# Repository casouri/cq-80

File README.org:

#+TITLE: CQ-80 Terminal (NAMACO端末) replica

Custom CQ-80 terminal replica! Not only is it 100% accurate, I also added Bluetooth music playback control feature. The shell is 3d printed, and the electronics are made of off-the-shelf parts.

This repository contains all the source files for the 3d model, PCB board design, etc. For a guide on making your own replica, visit: [[https://casouri.github.io/cq-80/guide-en.html][DIY Guide for CQ-80 Replica]].

For more pics, visit [[https://casouri.github.io/cq-80][CQ-80 Replica]].

#+attr_html: :width 100%
[[./docs/img/demo-top.jpeg]]

#+attr_html: :width 100%
[[./docs/img/cq-80 promo.jpg]]

#+attr_html: :width 100%
[[./docs/img/cq-80 screenshot.jpg]]

#+attr_html: :width 100%
[[./docs/img/demo-head-lamp.jpeg]]

#+attr_html: :width 100%
[[./docs/img/demo-side.jpeg]]

#+attr_html: :width 100%
[[./docs/img/demo-top-close-up.jpeg]]

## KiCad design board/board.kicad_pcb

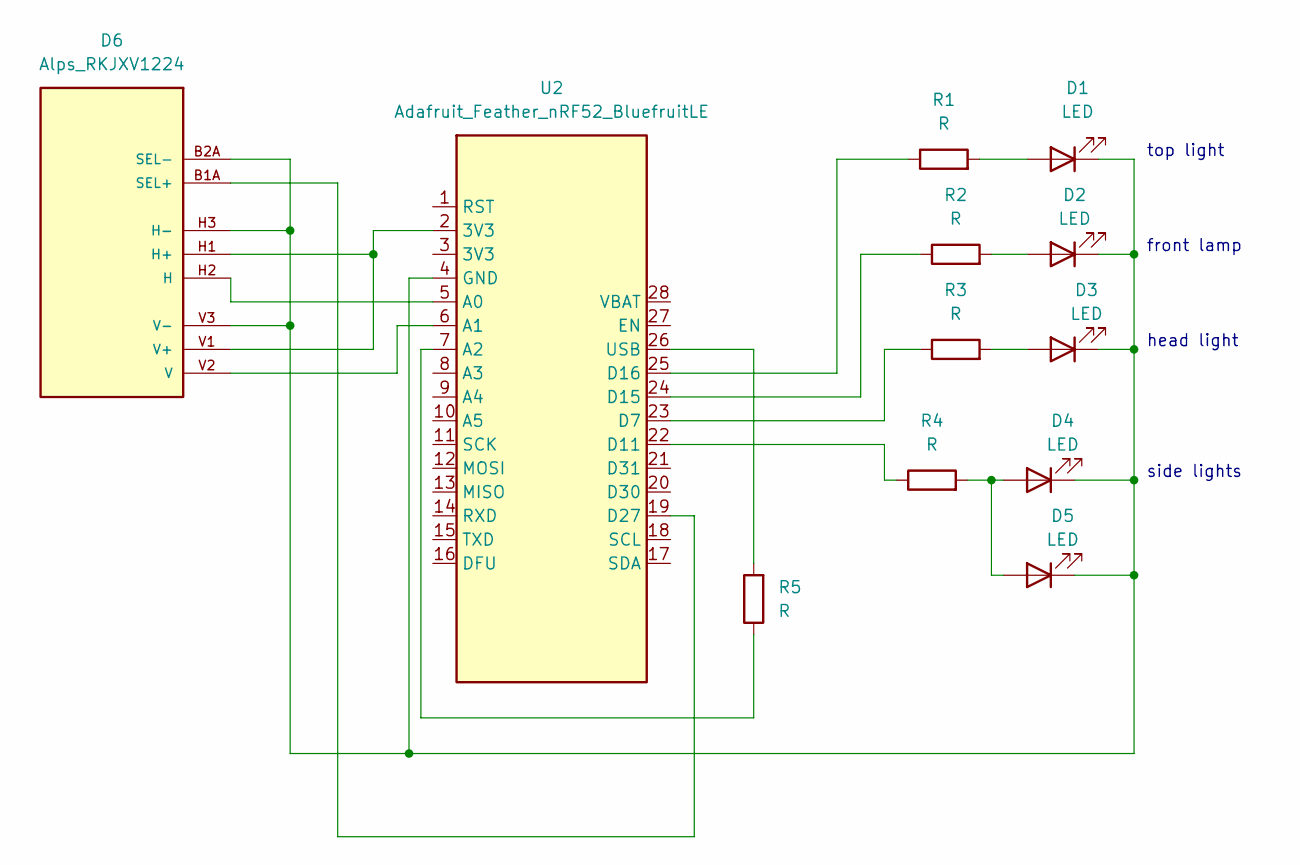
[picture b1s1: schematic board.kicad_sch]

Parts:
D1, D2, D3, D4, D5: LED; LED_D5.0mm_Clear
D6: Alps_RKJXV1224
R1, R2, R3, R4, R5: R; R_Axial_DIN0207_L6.3mm_D2.5mm_P10.16mm_Horizontal
U2: Adafruit_Feather_nRF52_BluefruitLE

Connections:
unnamed: D1.1 (K), D2.1 (K), D3.1 (K), D4.1 (K), D5.1 (K), D6.B2A (SEL-), D6.H3 (H-), D6.V3 (V-), U2.4 (GND)
unnamed: D1.2 (A), R1.2
unnamed: D2.2 (A), R2.2
unnamed: D3.2 (A), R3.2
unnamed: D4.2 (A), D5.2 (A), R4.2
unnamed: D6.B1A (SEL+), U2.19 (D27)
unnamed: D6.H1 (H+), D6.V1 (V+), U2.2 (3V3)
unnamed: D6.H2 (H), U2.5 (A0)
unnamed: D6.V2 (V), U2.6 (A1)
unnamed: R1.1, U2.25 (D16)
unnamed: R2.1, U2.24 (D15)
unnamed: R3.1, U2.23 (D7)
unnamed: R4.1, U2.22 (D11)
unnamed: R5.1, U2.7 (A2)
unnamed: R5.2, U2.26 (USB)

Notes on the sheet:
top light
front lamp
head light
side lights

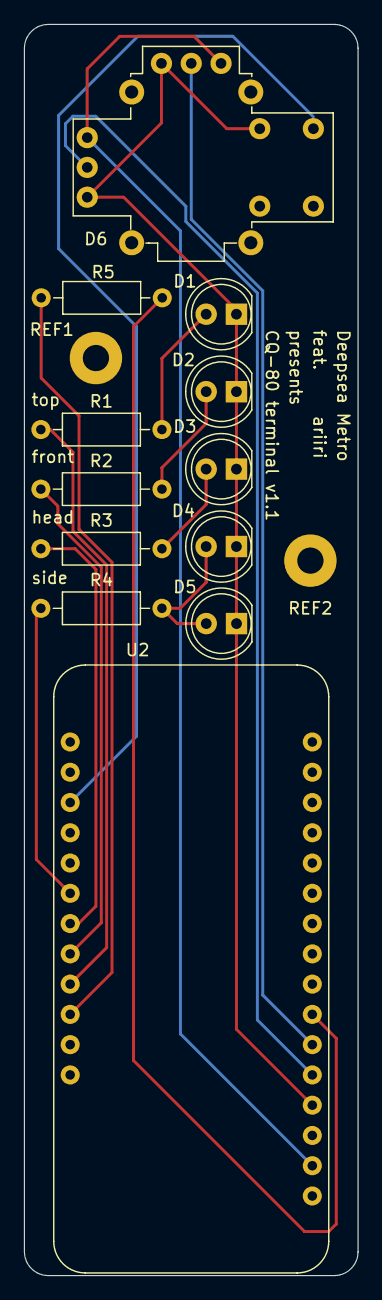
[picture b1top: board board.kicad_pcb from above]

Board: 2 copper layers, 28.0 x 105.0 mm, 14 parts (0 on the bottom side), 15 nets.

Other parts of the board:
REF1, REF2: MountingHole_2.2mm_M2_Pad

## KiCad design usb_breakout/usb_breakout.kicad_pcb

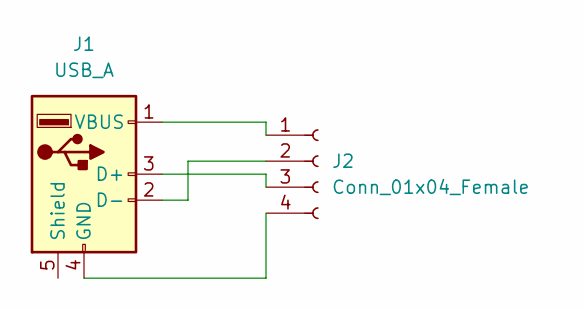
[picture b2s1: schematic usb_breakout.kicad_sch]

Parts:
J1: USB_A; USB_A_Molex_105057_Vertical
J2: Conn_01x04_Female; SolderWire-0.25sqmm_1x04_P4.2mm_D0.65mm_OD1.7mm

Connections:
unnamed: J1.1 (VBUS), J2.1
unnamed: J1.2 (D-), J2.2
unnamed: J1.3 (D+), J2.3
unnamed: J1.4 (GND), J2.4

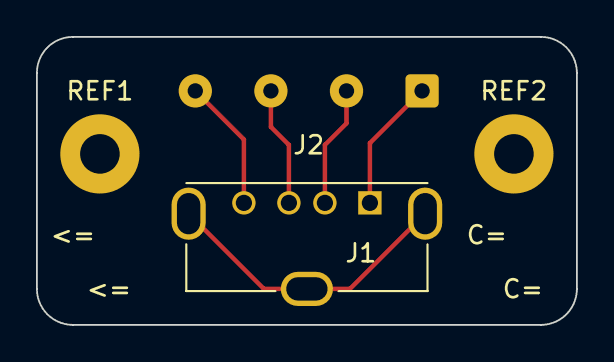
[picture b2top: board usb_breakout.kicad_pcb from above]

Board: 2 copper layers, 30.0 x 16.0 mm, 4 parts (0 on the bottom side), 4 nets.

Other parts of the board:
REF1, REF2: MountingHole_2.2mm_M2_Pad

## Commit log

2022-07-27 Add supports to top shell
2022-07-27 Before cutting grooves
2022-07-27 Cut all the grooves
2022-07-27 Fused all the bumps
2022-07-27 Slim-down top shell around joystick
2022-07-27 Fix joystick guard
2022-07-27 Revert back
2022-07-27 Slim-down top shell
2022-07-27 Fuse all supports
2022-07-27 Cut cutouts
2022-07-27 Cut grooves
2022-07-27 Fillet and cut trademark groove
2022-07-27 Fuse bump, cut cylinder
2022-07-27 Make trademark a separate part
2022-07-27 Top groove support
2022-07-27 Bottom & middle groove support
2022-07-27 Fix visibility
2022-07-27 Add middle groove support
2022-07-27 Add left right groove support
2022-07-27 Fuse groove supports
2022-07-27 Ready for bottom shell
2022-07-27 Screw support
2022-07-27 Fix screw support
2022-07-27 Add bottom
2022-07-27 Fix bottom shell thickness
2022-07-27 Add tail
2022-07-27 Hole in top shell
2022-07-28 Remove spreadsheet001
2022-07-28 Add lamp slots
2022-07-28 Rename bodies
2022-07-28 Adjust fitting of screw support
2022-07-28 Bottom screw support
2022-07-28 Bottom screw mirror
2022-07-28 Bottom grooves
2022-07-29 Bottom bumps
2022-07-29 Bottom alignment rails
2022-07-29 Adjust screw support
2022-07-29 Side rails
2022-07-29 Front rails
2022-07-29 Adjust front bars
2022-07-30 pcb support and usb port
2022-07-30 Add usb port
2022-07-30 Add pcb design for board and usb breakout
2022-07-30 Add font file
2022-07-31 Ready to merge
2022-07-31 Really ready to merge
2022-07-31 Cut bottom parts
2022-07-31 Move up cut master
2022-07-31 Adjust bottom screw support hole
2022-07-31 Fix usb port size
2022-07-31 Cut out tail fin
2022-07-31 Half way merging top
    Need to fix chin plate
2022-07-31 Adjust chin plate and fuse tail
2022-07-31 Fused and fixed
2022-07-31 Unmerged top shell
2022-07-31 Rework emboss support
2022-07-31 Rework tail
2022-07-31 Rework tail & screw support
2022-07-31 Fix trademark insert
2022-07-31 Rearrange bars
2022-08-01 Adjustments after prototype
2022-08-01 Add thumbstick
2022-08-02 Final changes
2022-08-03 Add arduino code
2022-08-04 Add timer sketch
2022-08-04 Fix voltage reading code
2022-08-04 * arduino/controller/controller.ino: Add battery indicator light
2022-08-04 * arduino/controller/controller.ino: Convert loop to timer.
2022-08-04 Use timer for top light blinking
    * arduino/controller/controller.ino: Change main loop blinking to
    timer-based blinking.
2022-08-04 Start battery check with fast inteval
    * arduino/controller/controller.ino: When system starts, use 1s
    interval for battery check, we can later change it to 1h when we go
    into sleep.
2022-08-04 Fix bottom tail thickness
2022-08-06 Add comment, change pause to 100ms
    * arduino/controller/controller.ino: As title.
2022-08-06 * arduino/controller/controller.ino: Add light toggle to up tilt.
2022-08-07 * arduino/controller/controller.ino: Rework events.
2022-08-09 * arduino/controller/controller.ino: Enable dcdc.
2022-08-09 * arduino/controller/controller.ino: Add back both state.
2022-08-09 * arduino/controller/controller.ino: Detect charging.
2022-08-09 * arduino/controller/controller.ino (lightPin): Change back.
2022-08-09 * arduino/controller/controller.ino: Refactor advertize blinking.
2022-08-09 * arduino/controller/controller.ino (advertize): Add slowcallback.
2022-08-09 * arduino/reader/reader.ino: Add usb reading.
2022-08-09 Cut materials (card, fin)
2022-08-09 Cut materials (tail support)
2022-08-09 Shrink & fix screw support
2022-08-09 * arduino/controller/controller.ino: Always light when joystick move
2022-08-09 * arduino/controller/controller.ino: More callback.
2022-08-09 * arduino/controller/controller.ino: Fix charging indicator logic.
2022-08-09 ; * arduino/reader/reader.ino: Minor change.
2022-08-10 Add color
2022-08-10 * board: Add usb pin and second side light led
2022-08-10 Add README
2022-08-10 * README.org (Table of contents): Add toc.
2022-08-10 init
2022-08-10 Move guide to github page
2022-08-10 Rename to docs
2022-08-10 * README.org: Add pointer to guide.
2022-08-10 Fix usb port support’s insert hole
2022-08-10 * docs/index.org: Fix description of M2 screws.
2022-08-10 Add chinese guide
2022-08-10 Update guides
2022-08-11 * docs/zh.org: Fix.
2023-02-11 Update doc
2023-02-11 Add README and demo
2023-02-11 Fix README image link
2023-02-11 Fix docs
2023-02-11 Minor doc change
2023-03-31 Update guide
2023-03-31 Fix link
